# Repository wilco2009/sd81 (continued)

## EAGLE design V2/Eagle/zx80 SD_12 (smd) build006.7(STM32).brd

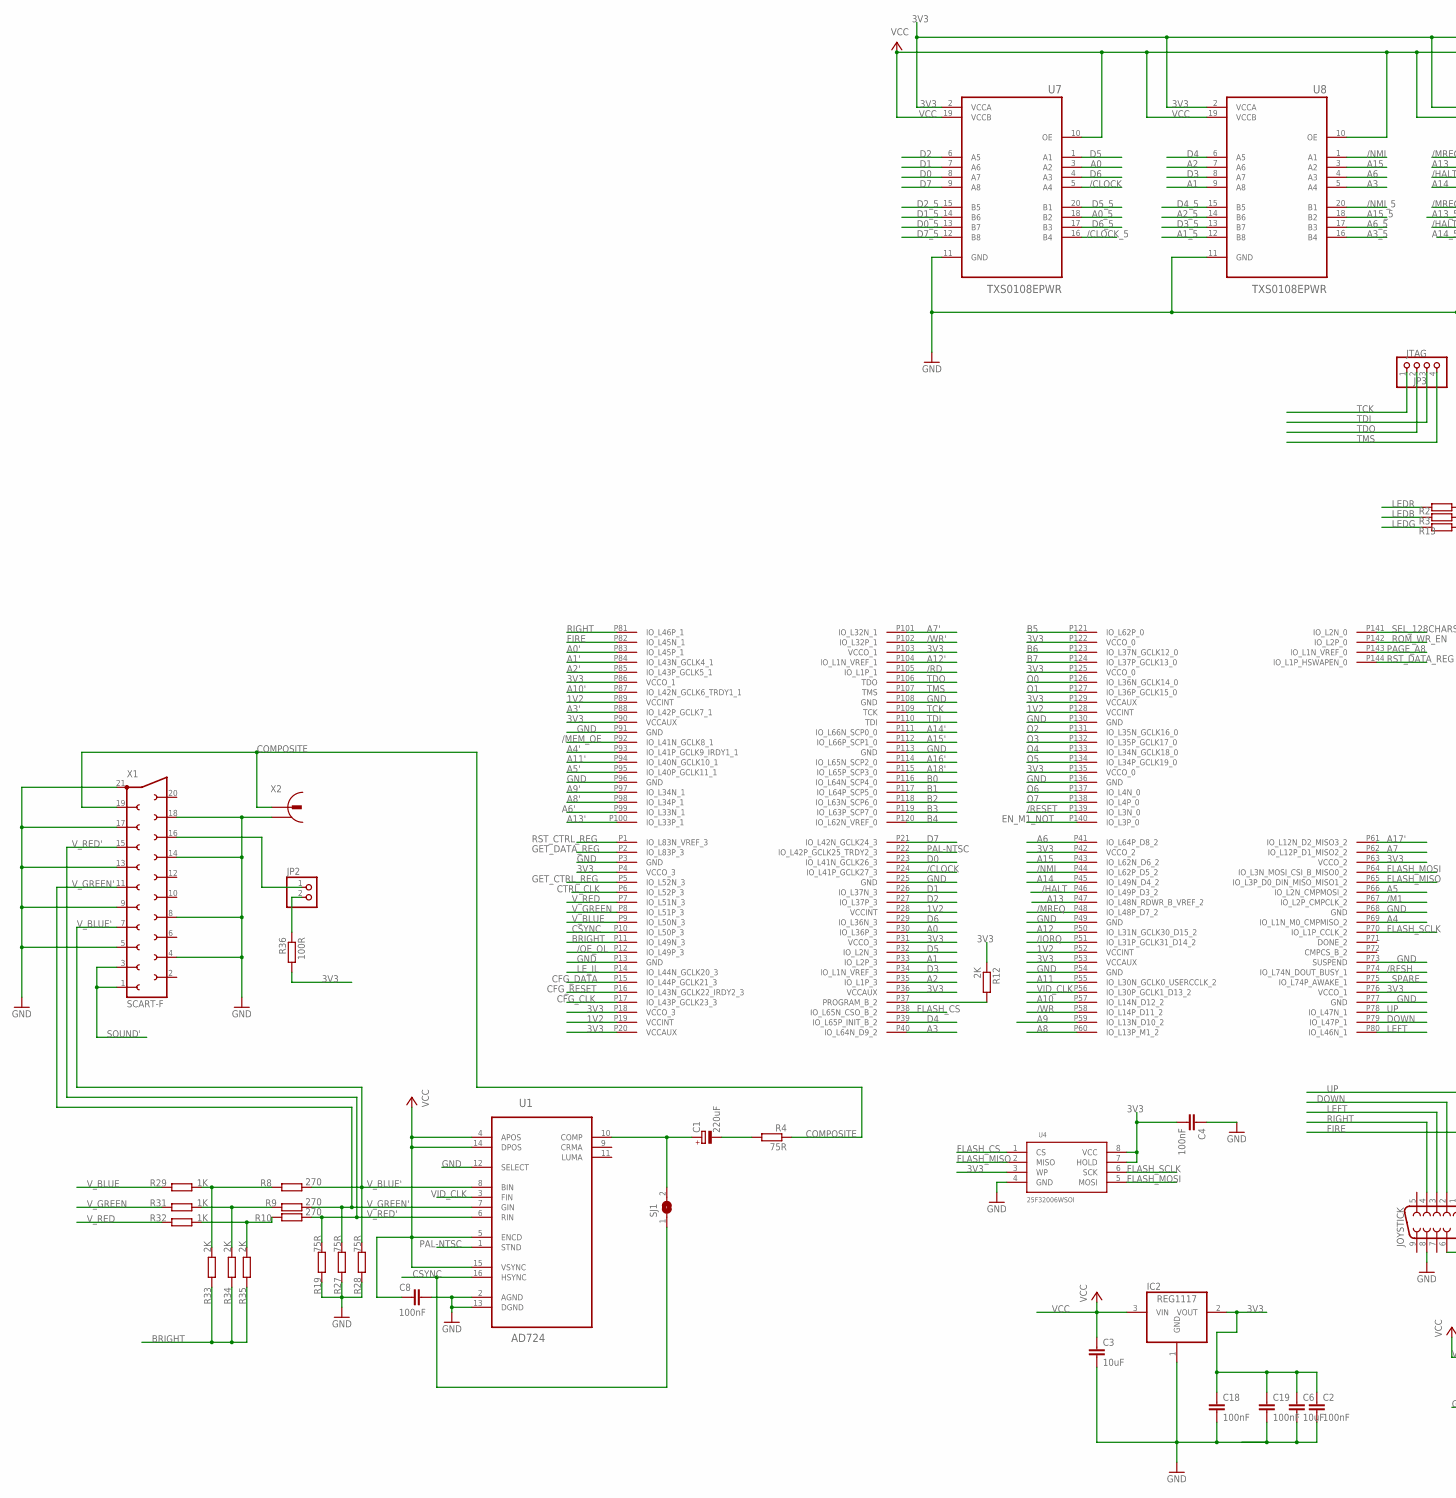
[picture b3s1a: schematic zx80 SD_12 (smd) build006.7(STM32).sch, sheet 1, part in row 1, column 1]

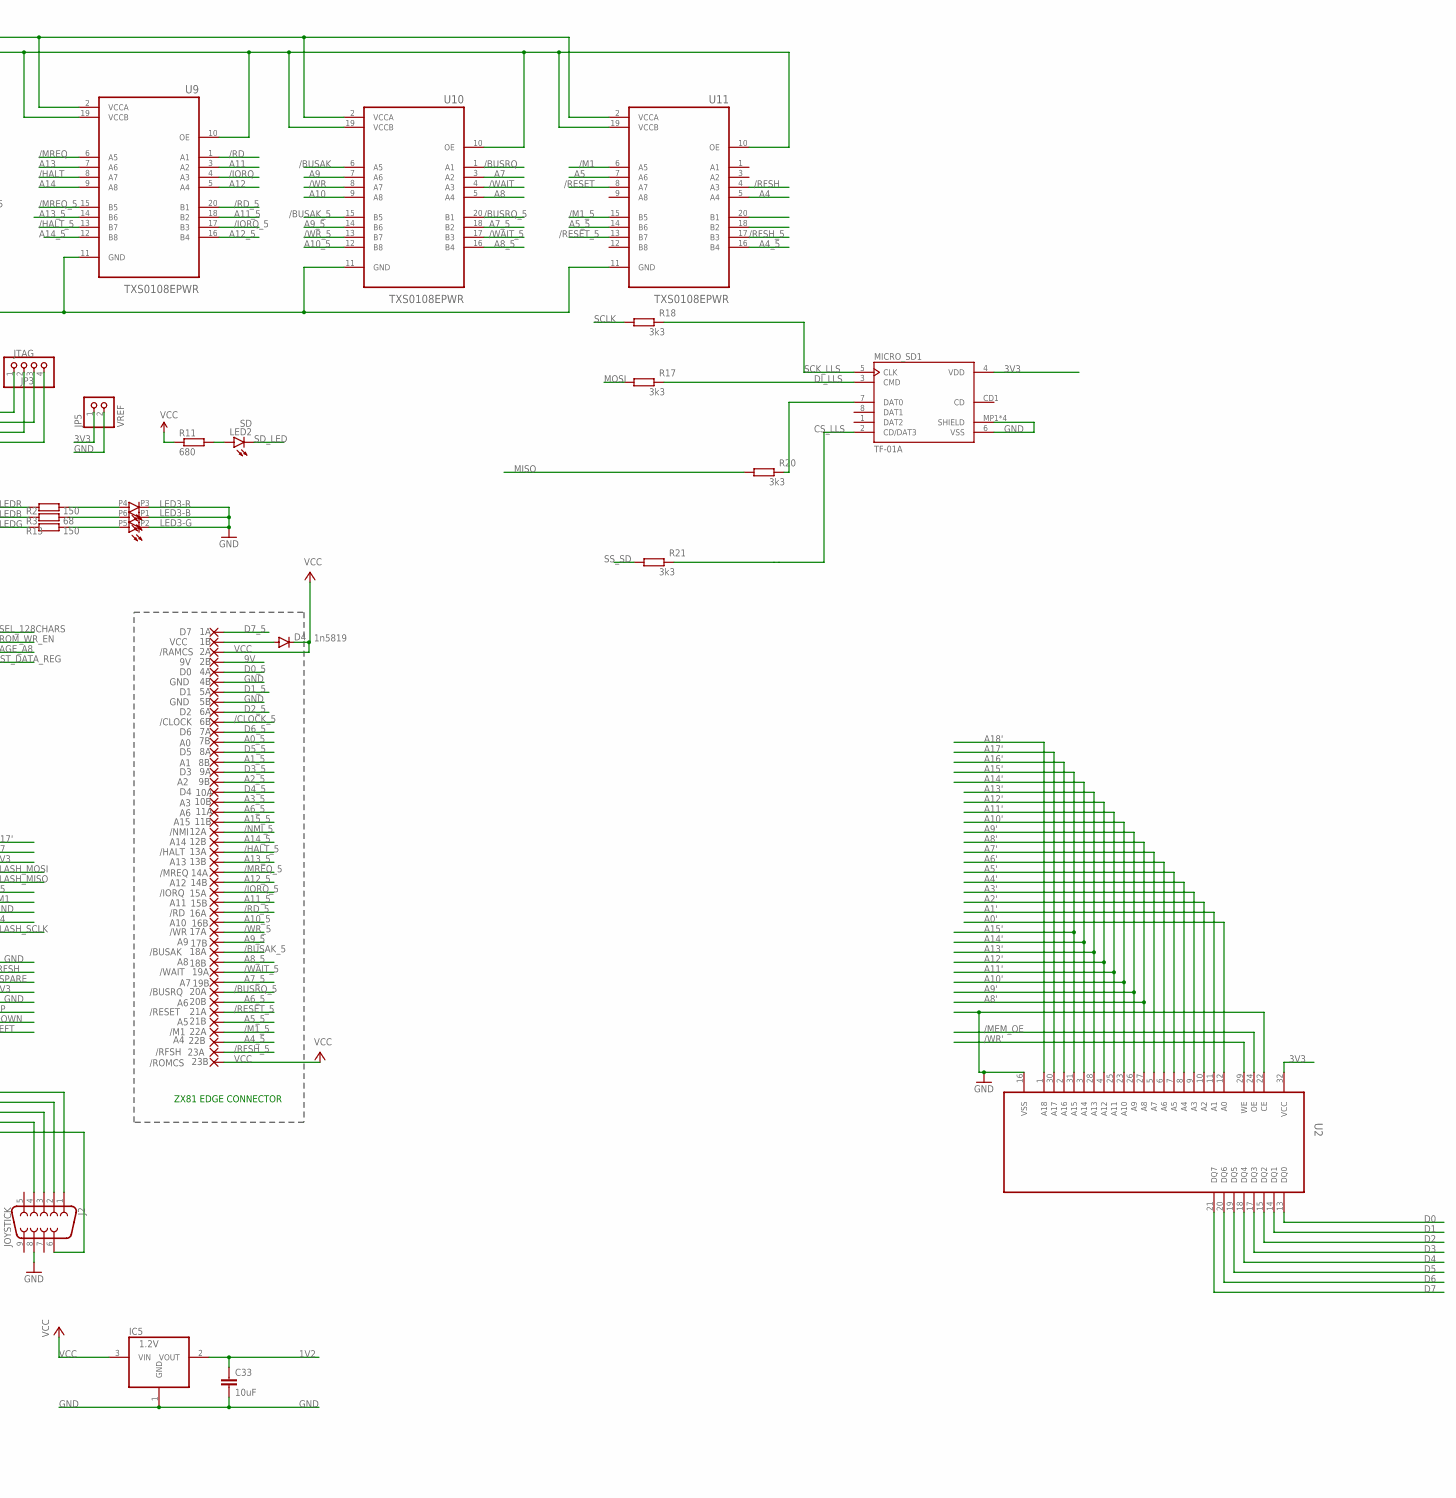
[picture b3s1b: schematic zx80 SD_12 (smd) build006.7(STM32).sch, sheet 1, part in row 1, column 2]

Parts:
1A: D7; EDGEPIN
1B: VCC; EDGEPIN
2A: /RAMCS; EDGEPIN
2B: 9V; EDGEPIN
4A: D0; EDGEPIN
4B, 5B: GND; EDGEPIN
5A: D1; EDGEPIN
6A: D2; EDGEPIN
6B: /CLOCK; EDGEPIN
7A: D6; EDGEPIN
7B: A0; EDGEPIN
8A: D5; EDGEPIN
8B: A1; EDGEPIN
9A: D3; EDGEPIN
9B: A2; EDGEPIN
10A: D4; EDGEPIN
10B: A3; EDGEPIN
11A, 20B: A6; EDGEPIN
11B: A15; EDGEPIN
12A: /NMI; EDGEPIN
12B: A14; EDGEPIN
13A: /HALT; EDGEPIN
13B: A13; EDGEPIN
14A: /MREQ; EDGEPIN
14B: A12; EDGEPIN
15A: /IORQ; EDGEPIN
15B: A11; EDGEPIN
16A: /RD; EDGEPIN
16B: A10; EDGEPIN
17A: /WR; EDGEPIN
17B: A9; EDGEPIN
18A: /BUSAK; EDGEPIN
18B: A8; EDGEPIN
19A: /WAIT; EDGEPIN
19B: A7; EDGEPIN
20A: /BUSRQ; EDGEPIN
21A: /RESET; EDGEPIN
21B: A5; EDGEPIN
22A: /M1; EDGEPIN
22B: A4; EDGEPIN
23A: /RFSH; EDGEPIN
23B: /ROMCS; EDGEPIN
C1: 220uF; UD-6,3X7,7_NICHICON
C2, C4, C18, C19: 100nF; C0603
C3, C6, C33: 10uF; C0603
C8: 100nF; C0603K
D4: 1n5819; SOD323-W
IC2: REG1117; SOT223
IC5: 1.2V; SOT223
J2: JOYSTICK; DB9_MALE
JP2: PINHD-1X2; 1X02
JP3: JTAG; 1X04
JP5: VREF; 1X02
LED2: SD; CHIPLED_0805
LED3: STATUS; 3535-PLCC6
MICRO_SD1: TF-01A
R2, R13: 150; R0603
R3: 68; R0603
R4, R19, R27, R28: 75R; R0603
R8, R9, R10: 270; R0603
R11: 680; R0603
R12, R33, R34, R35: 2K; R0402
R17, R18, R20, R21: 3k3; R0603
R29, R31, R32: 1K; R0402
R36: 100R; R0603
SJ1: SJ
U1: AD724; SOIC127P1032X265-16N
U2: AS6C4008; SOP32-5
U4: 25F32006WSOI; SO08-EIAJ
U6: XC6SLX9-2TQG144C; TQ144
U7, U8, U9, U10, U11: TXS0108EPWR; SOP65P640X120-20N
X1: SCART-F
X2: CON-CONRAD_736880-2P; 3P

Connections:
1V2: C33.1, IC5.2 (VOUT), U6.P19 (VCCINT), U6.P28 (VCCINT), U6.P52 (VCCINT), U6.P89 (VCCINT), U6.P128 (VCCINT)
3V3: C2.1, C4.2, C6.1, C18.1, C19.1, IC2.2 (VOUT), JP5.1, MICRO_SD1.4 (VDD), R12.1, R36.2, U2.32 (VCC), U4.3 (WP), U4.7 (HOLD), U4.8 (VCC), U6.P4 (VCCO_3), U6.P18 (VCCO_3), U6.P20 (VCCAUX), U6.P31 (VCCO_3), U6.P36 (VCCAUX), U6.P42 (VCCO_2), U6.P53 (VCCAUX), U6.P63 (VCCO_2), U6.P76 (VCCO_1), U6.P86 (VCCO_1), U6.P90 (VCCAUX), U6.P103 (VCCO_1), U6.P122 (VCCO_0), U6.P125 (VCCO_0), U6.P129 (VCCAUX), U6.P135 (VCCO_0), U7.2 (VCCA), U8.2 (VCCA), U9.2 (VCCA), U10.2 (VCCA), U11.2 (VCCA); also elsewhere on the board
9V: 2B.1
/BUSAK: U10.6 (A5)
/BUSAK_5: 18A.1, U10.15 (B5)
/BUSRQ: U10.1 (A1)
/BUSRQ_5: 20A.1, U10.20 (B1)
/CLOCK: U6.P24 (IO_L41P_GCLK27_3), U7.5 (A4)
/CLOCK_5: 6B.1, U7.16 (B4)
/HALT: U6.P46 (IO_L49P_D3_2), U9.8 (A7)
/HALT_5: 13A.1, U9.13 (B7)
/IORQ: U6.P51 (IO_L31P_GCLK31_D14_2), U9.4 (A3)
/IORQ_5: 15A.1, U9.17 (B3)
/M1: U6.P67 (IO_L2P_CMPCLK_2), U11.6 (A5)
/M1_5: 22A.1, U11.15 (B5)
/MEM_OE: U2.24 (OE), U6.P92 (IO_L41N_GCLK8_1)
/MREQ: U6.P48 (IO_L48P_D7_2), U9.6 (A5)
/MREQ_5: 14A.1, U9.15 (B5)
/NMI: U6.P44 (IO_L62P_D5_2), U8.1 (A1)
/NMI_5: 12A.1, U8.20 (B1)
/OE_OL: U6.P12 (IO_L49P_3); also elsewhere on the board
/RD: U6.P105 (IO_L1P_1), U9.1 (A1)
/RD_5: 16A.1, U9.20 (B1)
/RESET: U6.P139 (IO_L3N_0), U11.8 (A7); also elsewhere on the board
/RESET_5: 21A.1, U11.13 (B7)
/RFSH: U6.P74 (IO_L74N_DOUT_BUSY_1), U11.4 (A3)
/RFSH_5: 23A.1, U11.17 (B3)
/WAIT: U10.4 (A3); also elsewhere on the board
/WAIT_5: 19A.1, U10.17 (B3)
/WR: U6.P58 (IO_L14P_D11_2), U10.8 (A7)
/WR': U2.29 (WE), U6.P102 (IO_L32P_1); also elsewhere on the board
/WR_5: 17A.1, U10.13 (B7)
A0: U6.P30 (IO_L36P_3), U7.3 (A2)
A0': U2.12 (A0), U6.P83 (IO_L45P_1); also elsewhere on the board
A0_5: 7B.1, U7.18 (B2)
A1: U6.P33 (IO_L2P_3), U8.9 (A8)
A1': U2.11 (A1), U6.P84 (IO_L43N_GCLK4_1); also elsewhere on the board
A1_5: 8B.1, U8.12 (B8)
A2: U6.P35 (IO_L1P_3), U8.7 (A6)
A2': U2.10 (A2), U6.P85 (IO_L43P_GCLK5_1); also elsewhere on the board
A2_5: 9B.1, U8.14 (B6)
A3: U6.P40 (IO_L64N_D9_2), U8.5 (A4)
A3': U2.9 (A3), U6.P88 (IO_L42P_GCLK7_1); also elsewhere on the board
A3_5: 10B.1, U8.16 (B4)
A4: U6.P69 (IO_L1N_M0_CMPMISO_2), U11.5 (A4)
A4': U2.8 (A4), U6.P93 (IO_L41P_GCLK9_IRDY1_1); also elsewhere on the board
A4_5: 22B.1, U11.16 (B4)
A5: U6.P66 (IO_L2N_CMPMOSI_2), U11.7 (A6)
A5': U2.7 (A5), U6.P95 (IO_L40P_GCLK11_1); also elsewhere on the board
A5_5: 21B.1, U11.14 (B6)
A6: U6.P41 (IO_L64P_D8_2), U8.4 (A3)
A6': U2.6 (A6), U6.P99 (IO_L33N_1); also elsewhere on the board
A6_5: 11A.1, 20B.1, U8.17 (B3)
A7: U6.P62 (IO_L12P_D1_MISO2_2), U10.3 (A2)
A7': U2.5 (A7), U6.P101 (IO_L32N_1); also elsewhere on the board
A7_5: 19B.1, U10.18 (B2)
A8: U6.P60 (IO_L13P_M1_2), U10.5 (A4)
A8': U2.27 (A8), U6.P98 (IO_L34P_1); also elsewhere on the board
A8_5: 18B.1, U10.16 (B4)
A9: U6.P59 (IO_L13N_D10_2), U10.7 (A6)
A9': U2.26 (A9), U6.P97 (IO_L34N_1); also elsewhere on the board
A9_5: 17B.1, U10.14 (B6)
A10: U6.P57 (IO_L14N_D12_2), U10.9 (A8)
A10': U2.23 (A10), U6.P87 (IO_L42N_GCLK6_TRDY1_1); also elsewhere on the board
A10_5: 16B.1, U10.12 (B8)
A11: U6.P55 (IO_L30N_GCLK0_USERCCLK_2), U9.3 (A2)
A11': U2.25 (A11), U6.P94 (IO_L40N_GCLK10_1); also elsewhere on the board
A11_5: 15B.1, U9.18 (B2)
A12: U6.P50 (IO_L31N_GCLK30_D15_2), U9.5 (A4)
A12': U2.4 (A12), U6.P104 (IO_L1N_VREF_1); also elsewhere on the board
A12_5: 14B.1, U9.16 (B4)
A13: U6.P47 (IO_L48N_RDWR_B_VREF_2), U9.7 (A6)
A13': U2.28 (A13), U6.P100 (IO_L33P_1); also elsewhere on the board
A13_5: 13B.1, U9.14 (B6)
A14: U6.P45 (IO_L49N_D4_2), U9.9 (A8)
A14': U2.3 (A14), U6.P111 (IO_L66N_SCP0_0); also elsewhere on the board
A14_5: 12B.1, U9.12 (B8)
A15: U6.P43 (IO_L62N_D6_2), U8.3 (A2)
A15': U2.31 (A15), U6.P112 (IO_L66P_SCP1_0); also elsewhere on the board
A15_5: 11B.1, U8.18 (B2)
A16': U2.2 (A16), U6.P114 (IO_L65N_SCP2_0); also elsewhere on the board
A17': U2.30 (A17), U6.P61 (IO_L12N_D2_MISO3_2); also elsewhere on the board
A18': U2.1 (A18), U6.P115 (IO_L65P_SCP3_0); also elsewhere on the board
B0: U6.P116 (IO_L64N_SCP4_0); also elsewhere on the board
B1: U6.P117 (IO_L64P_SCP5_0); also elsewhere on the board
B2: U6.P118 (IO_L63N_SCP6_0); also elsewhere on the board
B3: U6.P119 (IO_L63P_SCP7_0); also elsewhere on the board
B4: U6.P120 (IO_L62N_VREF_0); also elsewhere on the board
B5: U6.P121 (IO_L62P_0); also elsewhere on the board
B6: U6.P123 (IO_L37N_GCLK12_0); also elsewhere on the board
B7: U6.P124 (IO_L37P_GCLK13_0); also elsewhere on the board
BRIGHT: R33.1, R34.1, R35.1, U6.P11 (IO_L49N_3)
CFG_CLK: U6.P17 (IO_L43P_GCLK23_3); also elsewhere on the board
CFG_DATA: U6.P15 (IO_L44P_GCLK21_3); also elsewhere on the board
CFG_RESET: U6.P16 (IO_L43N_GCLK22_IRDY2_3); also elsewhere on the board
COMPOSITE: R4.1, X1.19, X2.2 (1)
CSYNC: SJ1.1, U1.16 (HSYNC), U6.P10 (IO_L50P_3)
CS_LLS: MICRO_SD1.2 (CD/DAT3), R21.2
CTRL_CLK: U6.P6 (IO_L52P_3); also elsewhere on the board
D0: U2.13 (DQ0), U6.P23 (IO_L41N_GCLK26_3), U7.8 (A7)
D0_5: 4A.1, U7.13 (B7)
D1: U2.14 (DQ1), U6.P26 (IO_L37N_3), U7.7 (A6)
D1_5: 5A.1, U7.14 (B6)
D2: U2.15 (DQ2), U6.P27 (IO_L37P_3), U7.6 (A5)
D2_5: 6A.1, U7.15 (B5)
D3: U2.17 (DQ3), U6.P34 (IO_L1N_VREF_3), U8.8 (A7)
D3_5: 9A.1, U8.13 (B7)
D4: U2.18 (DQ4), U6.P39 (IO_L65P_INIT_B_2), U8.6 (A5)
D4_5: 10A.1, U8.15 (B5)
D5: U2.19 (DQ5), U6.P32 (IO_L2N_3), U7.1 (A1)
D5_5: 8A.1, U7.20 (B1)
D6: U2.20 (DQ6), U6.P29 (IO_L36N_3), U7.4 (A3)
D6_5: 7A.1, U7.17 (B3)
D7: U2.21 (DQ7), U6.P21 (IO_L42N_GCLK24_3), U7.9 (A8)
D7_5: 1A.1, U7.12 (B8)
DI_LLS: MICRO_SD1.3 (CMD), R17.2
DOWN: J2.2, U6.P79 (IO_L47P_1)
EN_M1_NOT: U6.P140 (IO_L3P_0); also elsewhere on the board
FIRE: J2.6, U6.P82 (IO_L45N_1)
FLASH_CS: U4.1 (CS), U6.P38 (IO_L65N_CSO_B_2)
FLASH_MISO: U4.2 (MISO), U6.P65 (IO_L3P_D0_DIN_MISO_MISO1_2)
FLASH_MOSI: U4.5 (MOSI), U6.P64 (IO_L3N_MOSI_CSI_B_MISO0_2)
FLASH_SCLK: U4.6 (SCK), U6.P70 (IO_L1P_CCLK_2)
GET_CTRL_REG: U6.P5 (IO_L52N_3); also elsewhere on the board
GET_DATA_REG: U6.P2 (IO_L83P_3); also elsewhere on the board
GND: 4B.1, 5B.1, C2.2, C3.2, C4.1, C6.2, C8.1, C18.2, C19.2, C33.2, IC2.1 (GND), IC5.1 (GND), J2.8, JP5.2, LED3.P1 (C), LED3.P2 (C), LED3.P3 (C), MICRO_SD1.6 (VSS), MICRO_SD1.MP1 (SHIELD), MICRO_SD1.MP2 (SHIELD), MICRO_SD1.MP3 (SHIELD), MICRO_SD1.MP4 (SHIELD), R19.2, R27.2, R28.2, U1.2 (AGND), U1.12 (SELECT), U1.13 (DGND), U2.16 (VSS), U2.22 (CE), U4.4 (GND), U6.P3 (GND), U6.P13 (GND), U6.P25 (GND), U6.P49 (GND), U6.P54 (GND), U6.P68 (GND), U6.P73 (SUSPEND), U6.P77 (GND), U6.P91 (GND), U6.P96 (GND), U6.P108 (GND), U6.P113 (GND), U6.P130 (GND), U6.P136 (GND), U7.11 (GND), U8.11 (GND), U9.11 (GND), U10.11 (GND), U11.11 (GND), X1.4, X1.5, X1.8, X1.9, X1.13, X1.14, X1.17, X1.18, X1.21, X2.1 (2); also elsewhere on the board
LEDB: R3.1; also elsewhere on the board
LEDG: R13.1; also elsewhere on the board
LEDR: R2.1; also elsewhere on the board
LEFT: J2.3, U6.P80 (IO_L46N_1)
LE_IL: U6.P14 (IO_L44N_GCLK20_3); also elsewhere on the board
MISO: R20.1; also elsewhere on the board
MOSI: R17.1; also elsewhere on the board
unnamed: C1.+, SJ1.2, U1.10 (COMP)
unnamed: MICRO_SD1.7 (DAT0), R20.2
unnamed: 1B.1, D4.A
unnamed: C1.-, R4.2
unnamed: R12.2, U6.P37 (PROGRAM_B_2)
unnamed: LED2.A, R11.2
unnamed: JP2.1, X1.16
unnamed: LED3.P4 (A), R2.2
unnamed: LED3.P6 (A), R3.2
unnamed: LED3.P5 (A), R13.2
unnamed: JP2.2, R36.1
unnamed: R8.2, R29.2, R33.2
unnamed: R9.2, R31.2, R34.2
unnamed: R10.2, R32.2, R35.2
O0: U6.P126 (IO_L36N_GCLK14_0); also elsewhere on the board
O1: U6.P127 (IO_L36P_GCLK15_0); also elsewhere on the board
O2: U6.P131 (IO_L35N_GCLK16_0); also elsewhere on the board
O3: U6.P132 (IO_L35P_GCLK17_0); also elsewhere on the board
O4: U6.P133 (IO_L34N_GCLK18_0); also elsewhere on the board
O5: U6.P134 (IO_L34P_GCLK19_0); also elsewhere on the board
O6: U6.P137 (IO_L4N_0); also elsewhere on the board
O7: U6.P138 (IO_L4P_0); also elsewhere on the board
PAGE_A8: U6.P143 (IO_L1N_VREF_0); also elsewhere on the board
PAL-NTSC: U1.1 (STND), U6.P22 (IO_L42P_GCLK25_TRDY2_3)
RIGHT: J2.4, U6.P81 (IO_L46P_1)
ROM_WR_EN: U6.P142 (IO_L2P_0); also elsewhere on the board
RST_CTRL_REG: U6.P1 (IO_L83N_VREF_3); also elsewhere on the board
RST_DATA_REG: U6.P144 (IO_L1P_HSWAPEN_0); also elsewhere on the board
SCK_LLS: MICRO_SD1.5 (CLK), R18.2
SCLK: R18.1; also elsewhere on the board
SD_LED: LED2.C; also elsewhere on the board
SEL_128CHARS: U6.P141 (IO_L2N_0); also elsewhere on the board
SOUND': X1.1, X1.3; also elsewhere on the board
SPARE: U6.P75 (IO_L74P_AWAKE_1)
SS_SD: R21.1; also elsewhere on the board
TCK: JP3.1, U6.P109 (TCK)
TDI: JP3.3, U6.P110 (TDI)
TDO: JP3.2, U6.P106 (TDO)
TMS: JP3.4, U6.P107 (TMS)
UP: J2.1, U6.P78 (IO_L47N_1)
VCC: 2A.1, 23B.1, C3.1, C8.2, D4.C, IC2.3 (VIN), IC5.3 (VIN), R11.1, U1.4 (APOS), U1.5 (ENCD), U1.14 (DPOS), U1.15 (VSYNC), U7.10 (OE), U7.19 (VCCB), U8.10 (OE), U8.19 (VCCB), U9.10 (OE), U9.19 (VCCB), U10.10 (OE), U10.19 (VCCB), U11.10 (OE), U11.19 (VCCB); also elsewhere on the board
VID_CLK: U1.3 (FIN), U6.P56 (IO_L30P_GCLK1_D13_2)
V_BLUE: R29.1, U6.P9 (IO_L50N_3)
V_BLUE': R8.1, R28.1, U1.8 (BIN), X1.7
V_GREEN: R31.1, U6.P8 (IO_L51P_3)
V_GREEN': R9.1, R27.1, U1.7 (GIN), X1.11
V_RED: R32.1, U6.P7 (IO_L51N_3)
V_RED': R10.1, R19.1, U1.6 (RIN), X1.15

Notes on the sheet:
ZX81 EDGE CONNECTOR

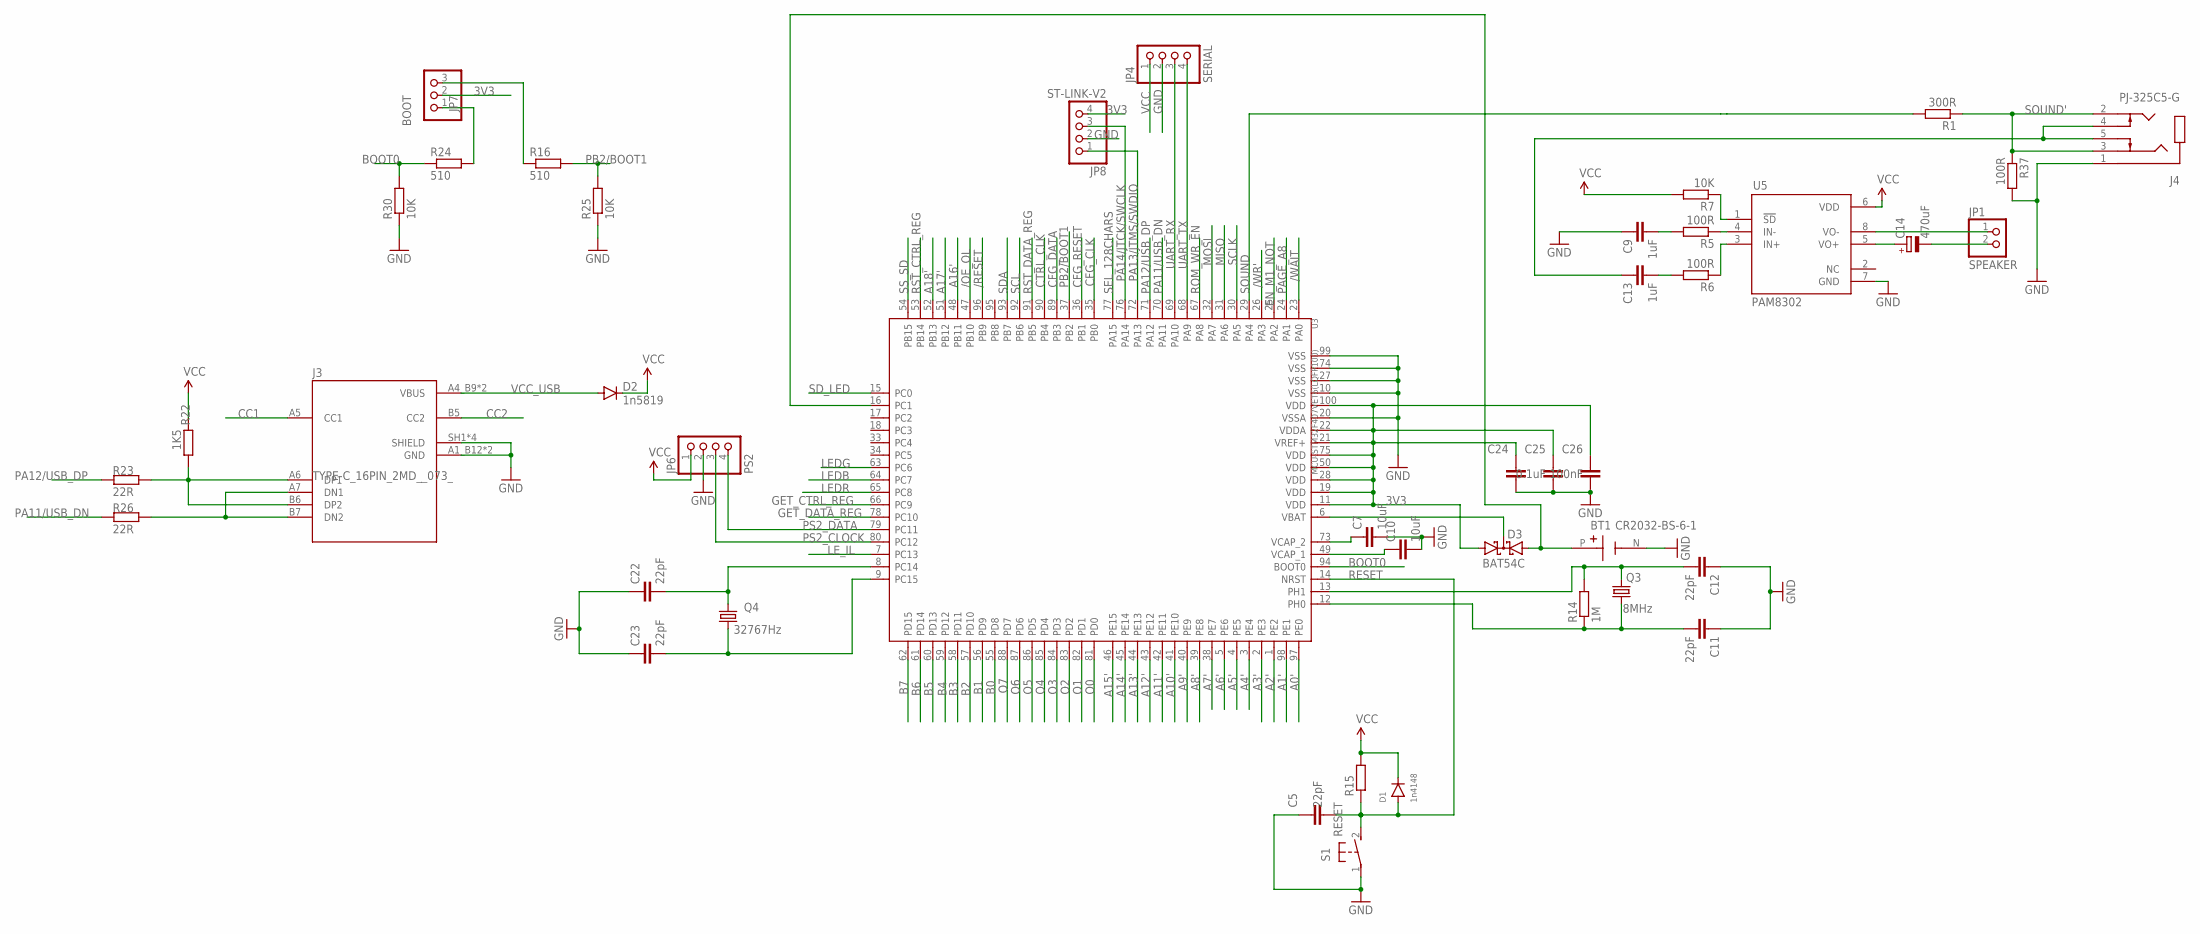
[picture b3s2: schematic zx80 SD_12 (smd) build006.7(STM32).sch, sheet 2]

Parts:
BT1: CR2032-BS-6-1; BAT_CR2032-BS-6-1
C5, C11, C12, C22, C23: 22pF; C0603
C7, C10: 10uF; C0603
C9, C13: 1uF; C0603
C14: 470uF; UD-6,3X7,7_NICHICON
C24, C25: 0.1uF; C0603
C26: 100nF; C0603
D1: 1n4148; SOD123
D2: 1n5819; SOD323-W
D3: BAT54C; SOT23
J3: TYPE-C_16PIN_2MD__073_; SHOUHAN_TYPE-C_16PIN_2MD__073_
J4: PJ-325C5-G; XKB_PJ-325C5-G
JP1: SPEAKER; 1X02
JP4: SERIAL; 1X04
JP6: PS2; 1X04
JP7: BOOT; 1X03
JP8: ST-LINK-V2; 1X04
Q3: 8MHz; 3.2X2.5_KX-7
Q4: 32767Hz; 3.2X1.5
R1: 300R; R0603
R5, R6, R37: 100R; R0603
R7, R25, R30: 10K; R0603
R14: 1M; R0402
R15: 3k3; R0603
R16, R24: 510; R0603
R22: 1K5; R0603
R23, R26: 22R; R0603
S1: RESET; B3F-31XX
U3: MCU-STM32F407VET6(LQFP100); LQFP100-0.5-13.8X13.8MM
U5: PAM8302; SOIC127P600X170-8N

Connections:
3V3: C24.1, C25.1, C26.1, D3.1 (A1), JP7.2, JP8.4, U3.11 (VDD), U3.19 (VDD), U3.21 (VREF+), U3.22 (VDDA), U3.28 (VDD), U3.50 (VDD), U3.75 (VDD), U3.100 (VDD); also elsewhere on the board
/OE_OL: U3.47 (PB10); also elsewhere on the board
/RESET: U3.96 (PB9); also elsewhere on the board
/WAIT: U3.23 (PA0); also elsewhere on the board
/WR': U3.26 (PA3); also elsewhere on the board
A0': U3.97 (PE0); also elsewhere on the board
A1': U3.98 (PE1); also elsewhere on the board
A2': U3.1 (PE2); also elsewhere on the board
A3': U3.2 (PE3); also elsewhere on the board
A4': U3.3 (PE4); also elsewhere on the board
A5': U3.4 (PE5); also elsewhere on the board
A6': U3.5 (PE6); also elsewhere on the board
A7': U3.38 (PE7); also elsewhere on the board
A8': U3.39 (PE8); also elsewhere on the board
A9': U3.40 (PE9); also elsewhere on the board
A10': U3.41 (PE10); also elsewhere on the board
A11': U3.42 (PE11); also elsewhere on the board
A12': U3.43 (PE12); also elsewhere on the board
A13': U3.44 (PE13); also elsewhere on the board
A14': U3.45 (PE14); also elsewhere on the board
A15': U3.46 (PE15); also elsewhere on the board
A16': U3.48 (PB11); also elsewhere on the board
A17': U3.51 (PB12); also elsewhere on the board
A18': U3.52 (PB13); also elsewhere on the board
B0: U3.55 (PD8); also elsewhere on the board
B1: U3.56 (PD9); also elsewhere on the board
B2: U3.57 (PD10); also elsewhere on the board
B3: U3.58 (PD11); also elsewhere on the board
B4: U3.59 (PD12); also elsewhere on the board
B5: U3.60 (PD13); also elsewhere on the board
B6: U3.61 (PD14); also elsewhere on the board
B7: U3.62 (PD15); also elsewhere on the board
BAT: BT1.P (POS), D3.2 (A2), U3.16 (PC1)
BOOT0: R24.1, R30.2, U3.94 (BOOT0)
CC1: J3.A5 (CC1)
CC2: J3.B5 (CC2)
CFG_CLK: U3.35 (PB0); also elsewhere on the board
CFG_DATA: U3.89 (PB3); also elsewhere on the board
CFG_RESET: U3.36 (PB1); also elsewhere on the board
CTRL_CLK: U3.90 (PB4); also elsewhere on the board
EN_M1_NOT: U3.25 (PA2); also elsewhere on the board
GET_CTRL_REG: U3.66 (PC9); also elsewhere on the board
GET_DATA_REG: U3.78 (PC10); also elsewhere on the board
GND: BT1.N (NEG), C5.1, C7.2, C9.1, C10.2, C11.1, C12.1, C22.1, C23.1, C24.2, C25.2, C26.2, J3.A1_B12 (GND), J3.B1_A12 (GND), J3.SH1 (SHIELD), J3.SH2 (SHIELD), J3.SH3 (SHIELD), J3.SH4 (SHIELD), J4.1, JP4.2, JP6.2, JP8.2, R25.1, R30.1, R37.2, S1.1, U3.10 (VSS), U3.20 (VSSA), U3.27 (VSS), U3.74 (VSS), U3.99 (VSS), U5.7 (GND); also elsewhere on the board
LEDB: U3.64 (PC7); also elsewhere on the board
LEDG: U3.63 (PC6); also elsewhere on the board
LEDR: U3.65 (PC8); also elsewhere on the board
LE_IL: U3.7 (PC13); also elsewhere on the board
MISO: U3.31 (PA6); also elsewhere on the board
MOSI: U3.32 (PA7); also elsewhere on the board
unnamed: J3.A6 (DP1), J3.B6 (DP2), R22.1, R23.1
unnamed: D3.3 (CC), U3.6 (VBAT)
unnamed: R6.1, U5.3 (IN+)
unnamed: R5.1, U5.4 (IN-)
unnamed: R7.1, U5.1 (!SD)
unnamed: C7.1, U3.73 (VCAP_2)
unnamed: J3.A7 (DN1), J3.B7 (DN2), R26.1
unnamed: C9.2, R5.2
unnamed: C13.2, R6.2
unnamed: C10.1, U3.49 (VCAP_1)
unnamed: C11.2, Q3.1, R14.1, U3.12 (PH0)
unnamed: C12.2, Q3.3 (2), R14.2, U3.13 (PH1)
unnamed: JP7.3, R16.1
unnamed: JP7.1, R24.2
unnamed: C22.2, Q4.2, U3.8 (PC14)
unnamed: C23.2, Q4.1, U3.9 (PC15)
unnamed: C14.+, U5.5 (VO+)
unnamed: JP1.1, U5.8 (VO-)
unnamed: C13.1, J4.4, J4.5
unnamed: C14.-, JP1.2
O0: U3.81 (PD0); also elsewhere on the board
O1: U3.82 (PD1); also elsewhere on the board
O2: U3.83 (PD2); also elsewhere on the board
O3: U3.84 (PD3); also elsewhere on the board
O4: U3.85 (PD4); also elsewhere on the board
O5: U3.86 (PD5); also elsewhere on the board
O6: U3.87 (PD6); also elsewhere on the board
O7: U3.88 (PD7); also elsewhere on the board
PA11/USB_DN: R26.2, U3.70 (PA11)
PA12/USB_DP: R23.2, U3.71 (PA12)
PA13/JTMS/SWDIO: JP8.1, U3.72 (PA13)
PA14/JTCK/SWCLK: JP8.3, U3.76 (PA14)
PAGE_A8: U3.24 (PA1); also elsewhere on the board
PB2/BOOT1: R16.2, R25.2, U3.37 (PB2)
PS2_CLOCK: JP6.3, U3.80 (PC12)
PS2_DATA: JP6.4, U3.79 (PC11)
RESET: C5.2, D1.A, R15.1, S1.2 (S), U3.14 (NRST)
ROM_WR_EN: U3.67 (PA8); also elsewhere on the board
RST_CTRL_REG: U3.53 (PB14); also elsewhere on the board
RST_DATA_REG: U3.91 (PB5); also elsewhere on the board
SCL: U3.92 (PB6)
SCLK: U3.30 (PA5); also elsewhere on the board
SDA: U3.93 (PB7)
SD_LED: U3.15 (PC0); also elsewhere on the board
SEL_128CHARS: U3.77 (PA15); also elsewhere on the board
SOUND: R1.2, U3.29 (PA4)
SOUND': J4.2, J4.3, R1.1, R37.1; also elsewhere on the board
SS_SD: U3.54 (PB15); also elsewhere on the board
UART_RX: JP4.3, U3.69 (PA10)
UART_TX: JP4.4, U3.68 (PA9)
VCC: D1.C, D2.C, JP4.1, JP6.1, R7.2, R15.2, R22.2, U5.6 (VDD); also elsewhere on the board
VCC_USB: D2.A, J3.A4_B9 (VBUS), J3.B4_A9 (VBUS)

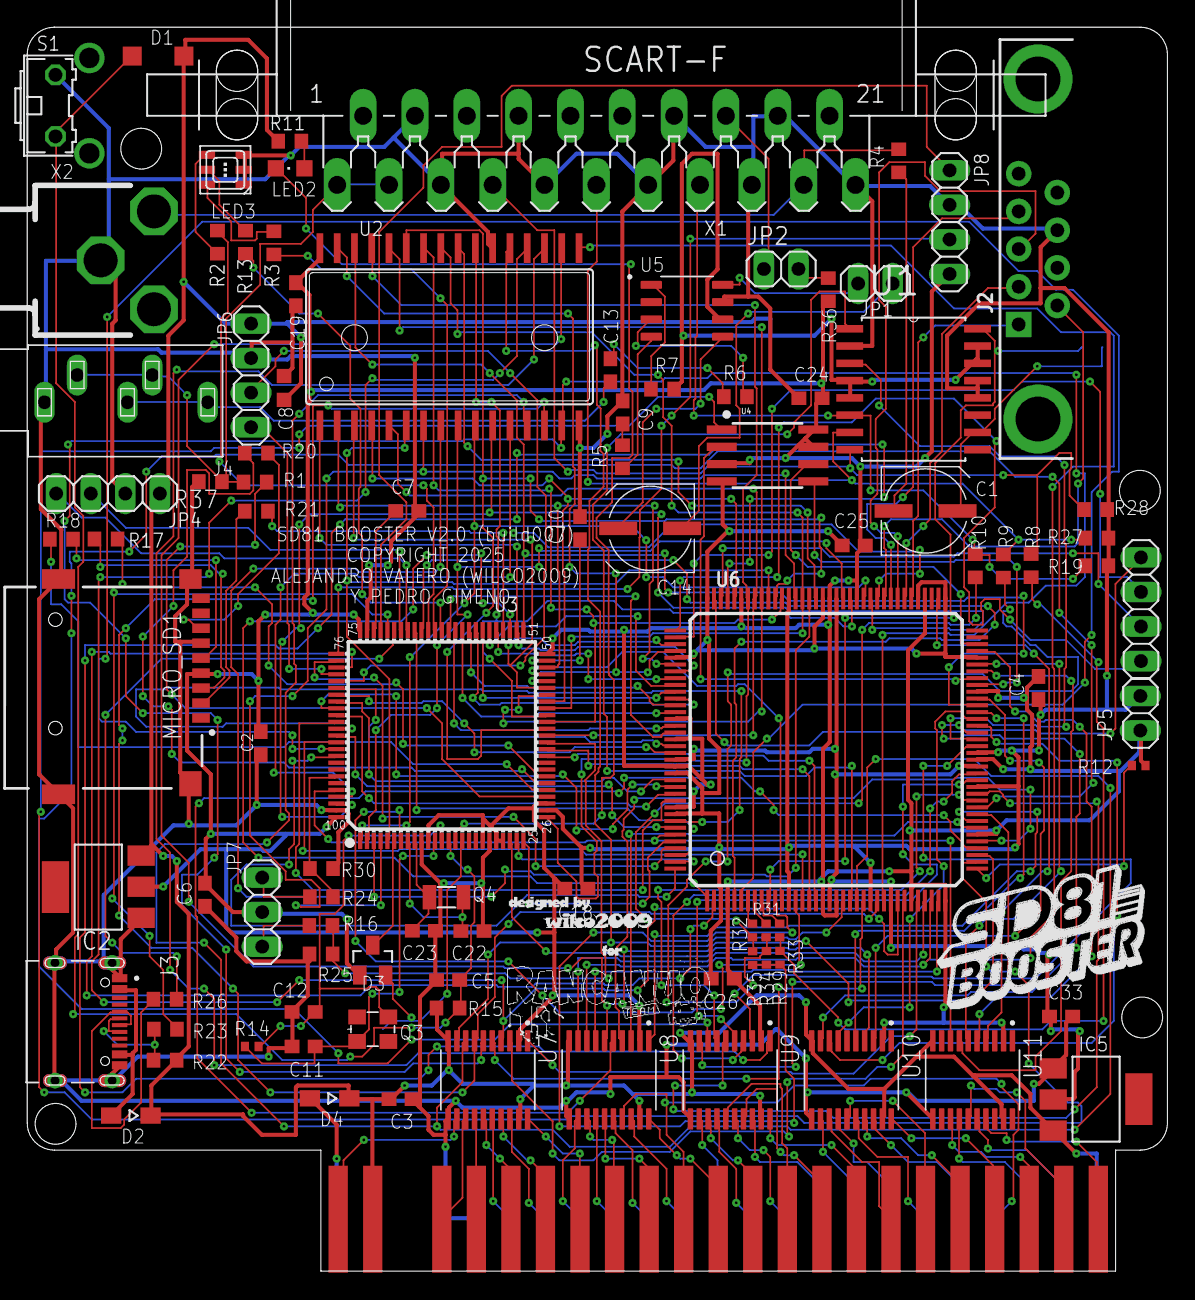
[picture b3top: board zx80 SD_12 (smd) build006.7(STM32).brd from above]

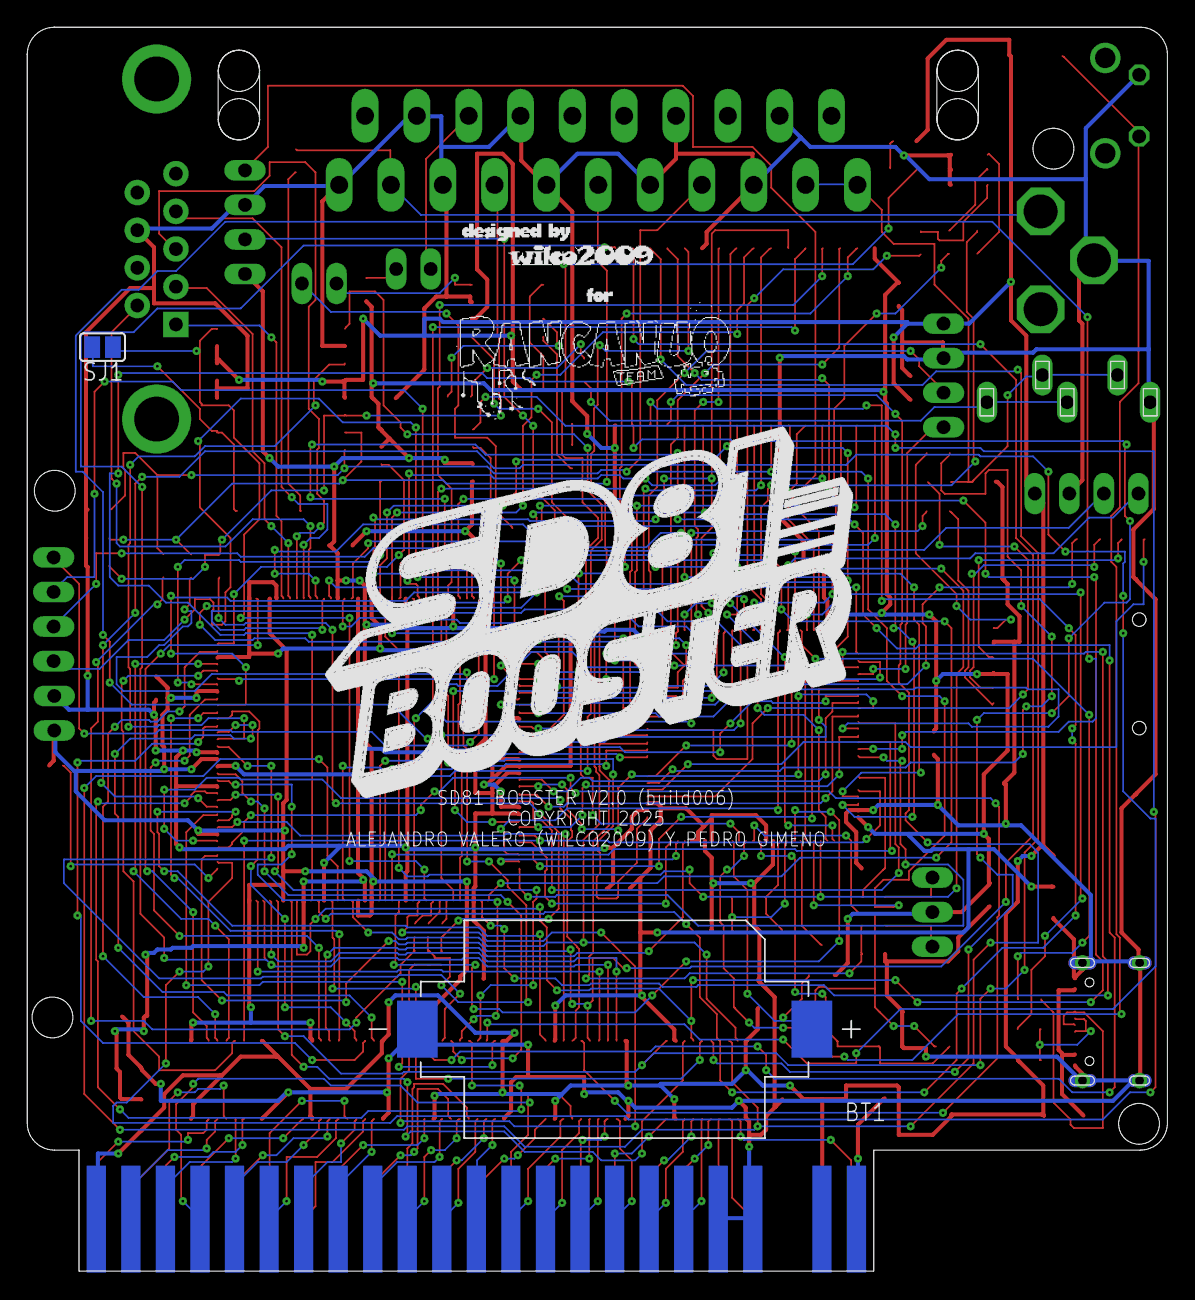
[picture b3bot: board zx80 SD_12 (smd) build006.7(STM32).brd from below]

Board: 2 copper layers, 83.8 x 91.4 mm, 141 parts (24 on the bottom side), 211 nets.
